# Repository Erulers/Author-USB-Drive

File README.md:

# Author-USB-Drive
8GB USB drive with Kicad files.

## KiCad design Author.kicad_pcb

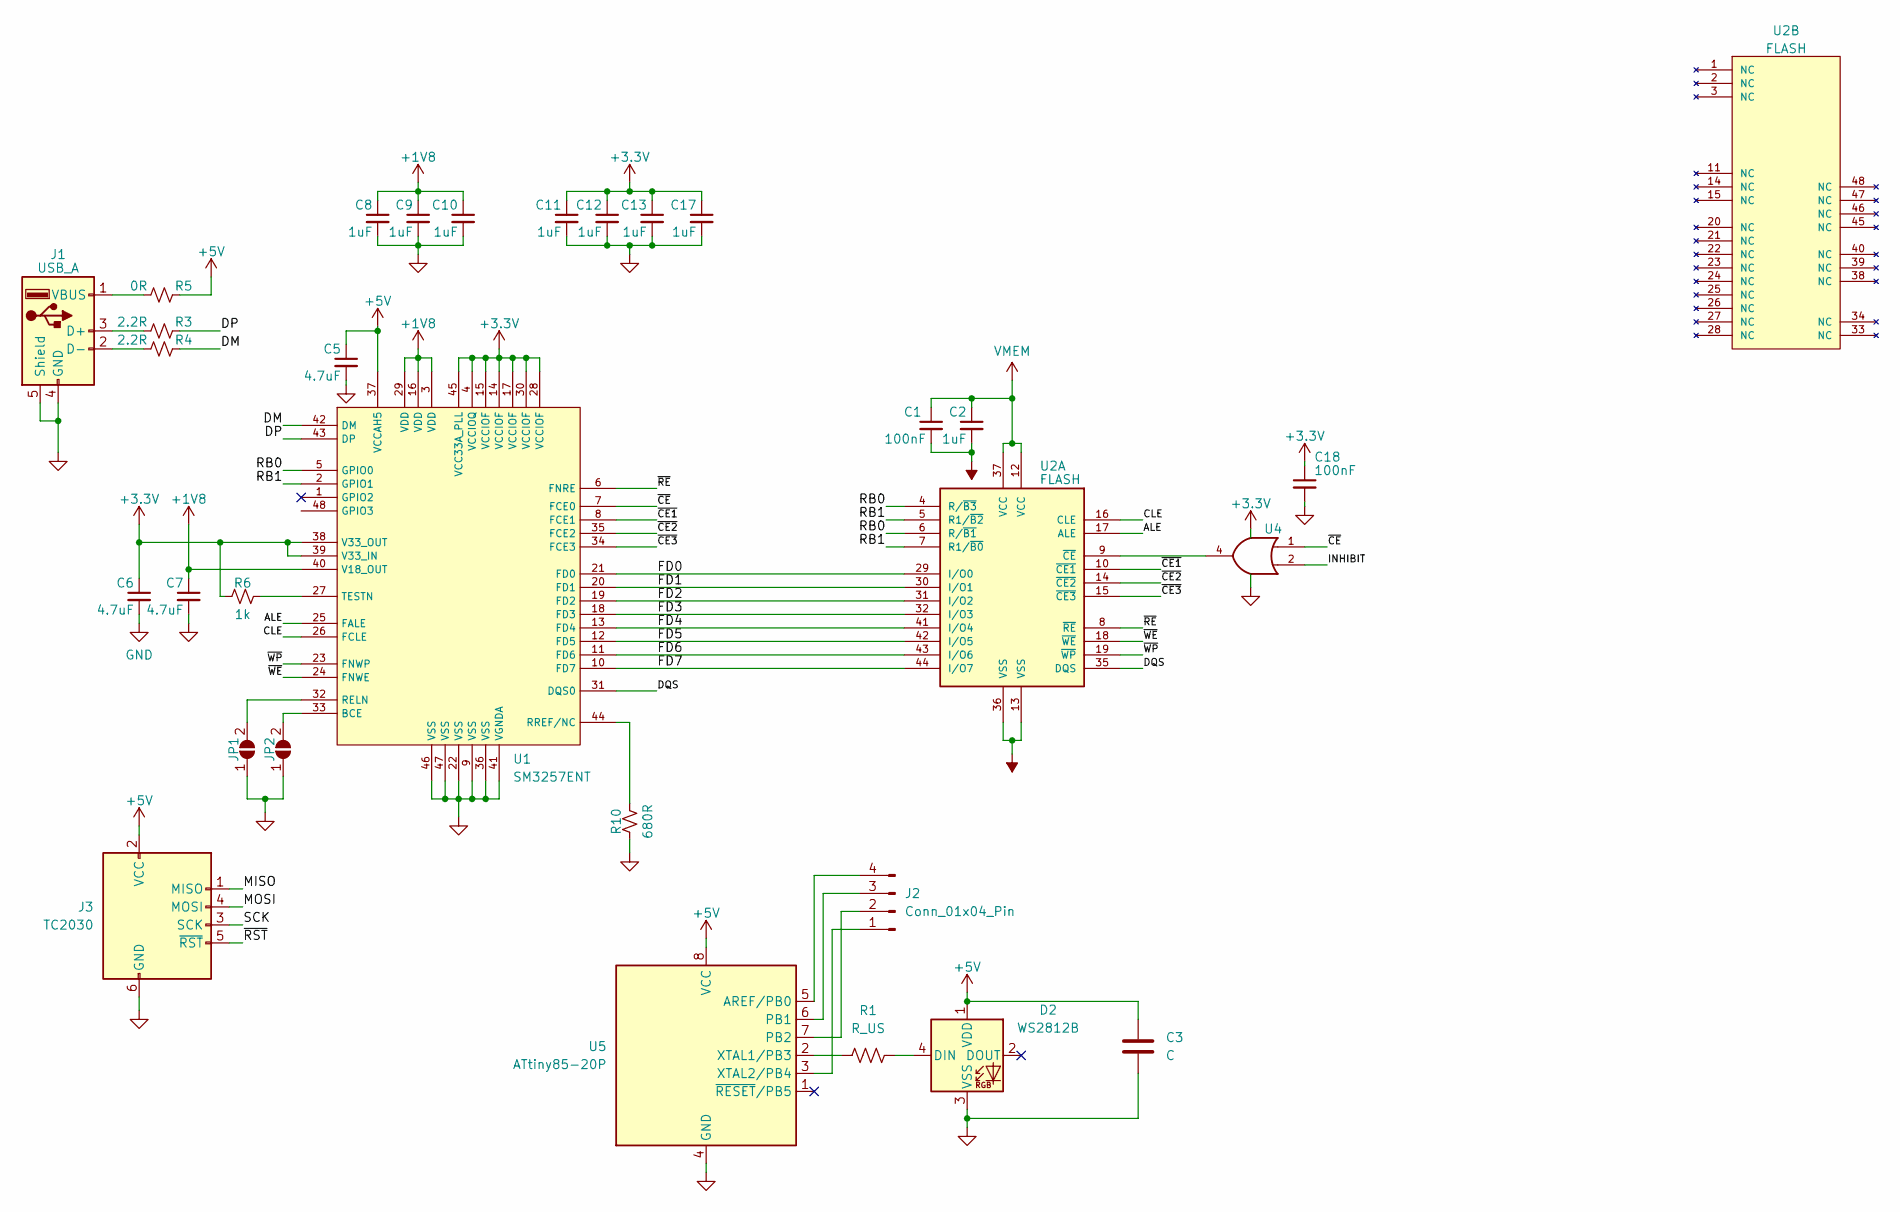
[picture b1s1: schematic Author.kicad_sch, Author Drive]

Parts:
C1, C18: 100nF; C_0603_1608Metric; MPN CC0603KRX7R7BB104
C2, C8, C9, C10, C11, C12, C13, C17: 1uF; C_0603_1608Metric; MPN CC0603KRX7R7BB105
C3: C; C_0201_0603Metric
C5, C6, C7: 4.7uF; C_0603_1608Metric; MPN CL10A475KP8NNNC
D2: WS2812B; LED_WS2812B_PLCC4_5.0x5.0mm_P3.2mm
J1: USB_A; USB_A_CNCTech_1001-011-01101_Horizontal; MPN 0480372200
J2: Conn_01x04_Pin; PinHeader_1x04_P1.27mm_Vertical
J3: TC2030; Tag-Connect_TC2030-IDC-NL_2x03_P1.27mm_Vertical; MPN TC2030
JP1, JP2: SolderJumper_2_Open; SolderJumper-2_P1.3mm_Open_Pad1.0x1.5mm
R1: R_US; R_0201_0603Metric
R3, R4: 2.2R; R_0603_1608Metric; MPN RC0603FR-072R2L
R5: 0R; R_0603_1608Metric; MPN RC0603FR-070RL
R6: 1k; R_0603_1608Metric; MPN RC0603FR-071KL
R10: 680R; R_0603_1608Metric; MPN RC0603FR-07680RL
U1: SM3257ENT; TQFP-48_7x7mm_P0.5mm; MPN SM3257ENAA
U2: FLASH; TSOP-I-48_14.4x12mm_P0.5mm; MPN MT29F64G08CBABAWP
U4: SN74LVC1G32DCKR; SOT-353_SC-70-5; MPN SN74LVC1G32DCKR
U5: ATtiny85-20P; DIP-8_W7.62mm

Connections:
+1V8: C7.1, C8.1, C9.1, C10.1, U1.3 (VDD), U1.16 (VDD), U1.29 (VDD), U1.40 (V18_OUT)
+3.3V: C6.1, C11.1, C12.1, C13.1, C17.1, C18.1, R6.1, U1.4 (VCCIOQ), U1.14 (VCCIOF), U1.15 (VCCIOF), U1.17 (VCCIOF), U1.28 (VCCIOF), U1.30 (VCCIOF), U1.38 (V33_OUT), U1.39 (V33_IN), U1.45 (VCC33A_PLL), U4.5 (VCC)
+5V: C3.1, C5.1, D2.1 (VDD), J3.2 (VCC), R5.2, U1.37 (VCCAH5), U5.8 (VCC)
/ALE: U1.25 (FALE), U2.17 (ALE)
/CLE: U1.26 (FCLE), U2.16 (CLE)
/DM: R4.2, U1.42 (DM)
/DP: R3.2, U1.43 (DP)
/DQS: U1.31 (DQS0), U2.35 (DQS)
/FD0: U1.21 (FD0), U2.29 (I/O0)
/FD1: U1.20 (FD1), U2.30 (I/O1)
/FD2: U1.19 (FD2), U2.31 (I/O2)
/FD3: U1.18 (FD3), U2.32 (I/O3)
/FD4: U1.13 (FD4), U2.41 (I/O4)
/FD5: U1.12 (FD5), U2.42 (I/O5)
/FD6: U1.11 (FD6), U2.43 (I/O6)
/FD7: U1.10 (FD7), U2.44 (I/O7)
/INHIBIT: U4.2
/MISO: J3.1 (MISO)
/MOSI: J3.4 (MOSI)
/RB0: U1.5 (GPIO0), U2.4 (R/~B3), U2.6 (R/~B1)
/RB1: U1.2 (GPIO1), U2.5 (R1/~B2), U2.7 (R1/~B0)
/SCK: J3.3 (SCK)
/~CE1: U1.8 (FCE1), U2.10 (~CE1)
/~CE2: U1.35 (FCE2), U2.14 (~CE2)
/~CE3: U1.34 (FCE3), U2.15 (~CE3)
/~CE: U1.7 (FCE0), U4.1
/~RE: U1.6 (FNRE), U2.8 (~RE)
/~RST: J3.5 (~RST)
/~WE: U1.24 (FNWE), U2.18 (~WE)
/~WP: U1.23 (FNWP), U2.19 (~WP)
GND: C3.2, C5.2, C6.2, C7.2, C8.2, C9.2, C10.2, C11.2, C12.2, C13.2, C17.2, C18.2, D2.3 (VSS), J1.4 (GND), J1.5 (Shield), J3.6 (GND), JP1.1 (A), JP2.1 (A), R10.1, U1.9 (VSS), U1.22 (VSS), U1.36 (VSS), U1.41 (VGNDA), U1.46 (VSS), U1.47 (VSS), U4.3 (GND), U5.4 (GND)
unnamed: D2.4 (DIN), R1.2
unnamed: J1.3 (D+), R3.1
unnamed: J1.2 (D-), R4.1
unnamed: J1.1 (VBUS), R5.1
unnamed: J2.1, U5.3 (XTAL2/PB4)
unnamed: J2.2, U5.7 (PB2)
unnamed: J2.3, U5.6 (PB1)
unnamed: J2.4, U5.5 (AREF/PB0)
unnamed: JP1.2 (B), U1.32 (RELN)
unnamed: JP2.2 (B), U1.33 (BCE)
unnamed: R10.2, U1.44 (RREF/NC)
unnamed: R6.2, U1.27 (TESTN)
unnamed: U2.9 (~CE), U4.4
unnamed: R1.1, U5.2 (XTAL1/PB3)
VMEM: C1.1, C2.1, U2.12 (VCC), U2.37 (VCC)
VS: C1.2, C2.2, U2.13 (VSS), U2.36 (VSS)

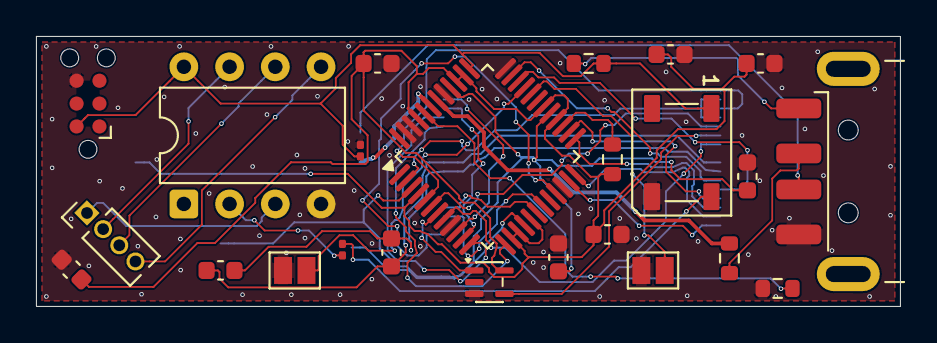
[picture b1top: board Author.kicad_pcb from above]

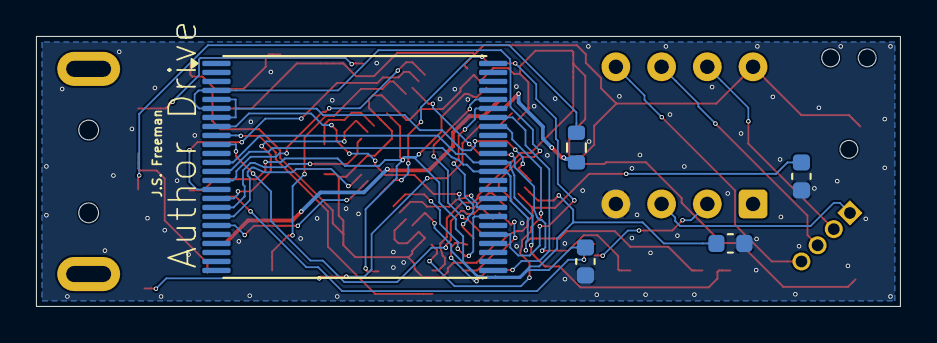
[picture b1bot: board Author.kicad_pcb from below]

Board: 2 copper layers, 48.0 x 15.0 mm, 29 parts (5 on the bottom side), 42 nets.
